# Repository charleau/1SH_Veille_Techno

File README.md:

# 1SH Veille Technologique
 
## L'électronique fondamentale

### Contexte
La technologie est omniprésente dans la vie de chacun. Les circuits imprimés et les composantes électroniques sont le point central de cette technologie. Avec l'essor des technologies telles que l'Internet des objets (IoT), les véhicules autonomes, et la robotique, etc., la demande en systèmes électroniques efficaces et fiables n'a jamais été aussi élevée. La compréhension des principes fondamentaux ainsi que les composantes électronique est donc nécessaire.

### Objectif
Connaitre et comprendre le fonctionnement de chacun des composants de base essentiels en électronique.
- Utilité des composants
- Fonctionnement des composants
- Schéma de circuit imprimé
- Exemples d'utilisation

### Démarche de [recherche](https://github.com/charleau/1SH_Veille_Techno/blob/main/Recherches.md)
- Phase I
    - [Lister les différents composants](https://github.com/charleau/1SH_Veille_Techno/blob/main/Recherches.md#composantes)
    - Identifier leur utilité
- Phase II
    - Comprendre le fonctionnement des composants
    - [Démontrer la bonne façon de brancher les composants](https://github.com/charleau/1SH_Veille_Techno/blob/main/Recherches.md#sch%C3%A9ma-%C3%A9lectrique)
- Phase III
    - [Concevoir un schéma de circuit appliquant les composants de base](https://github.com/charleau/1SH_Veille_Techno/blob/main/Recherches.md#conception-du-circuit-imprim%C3%A9)

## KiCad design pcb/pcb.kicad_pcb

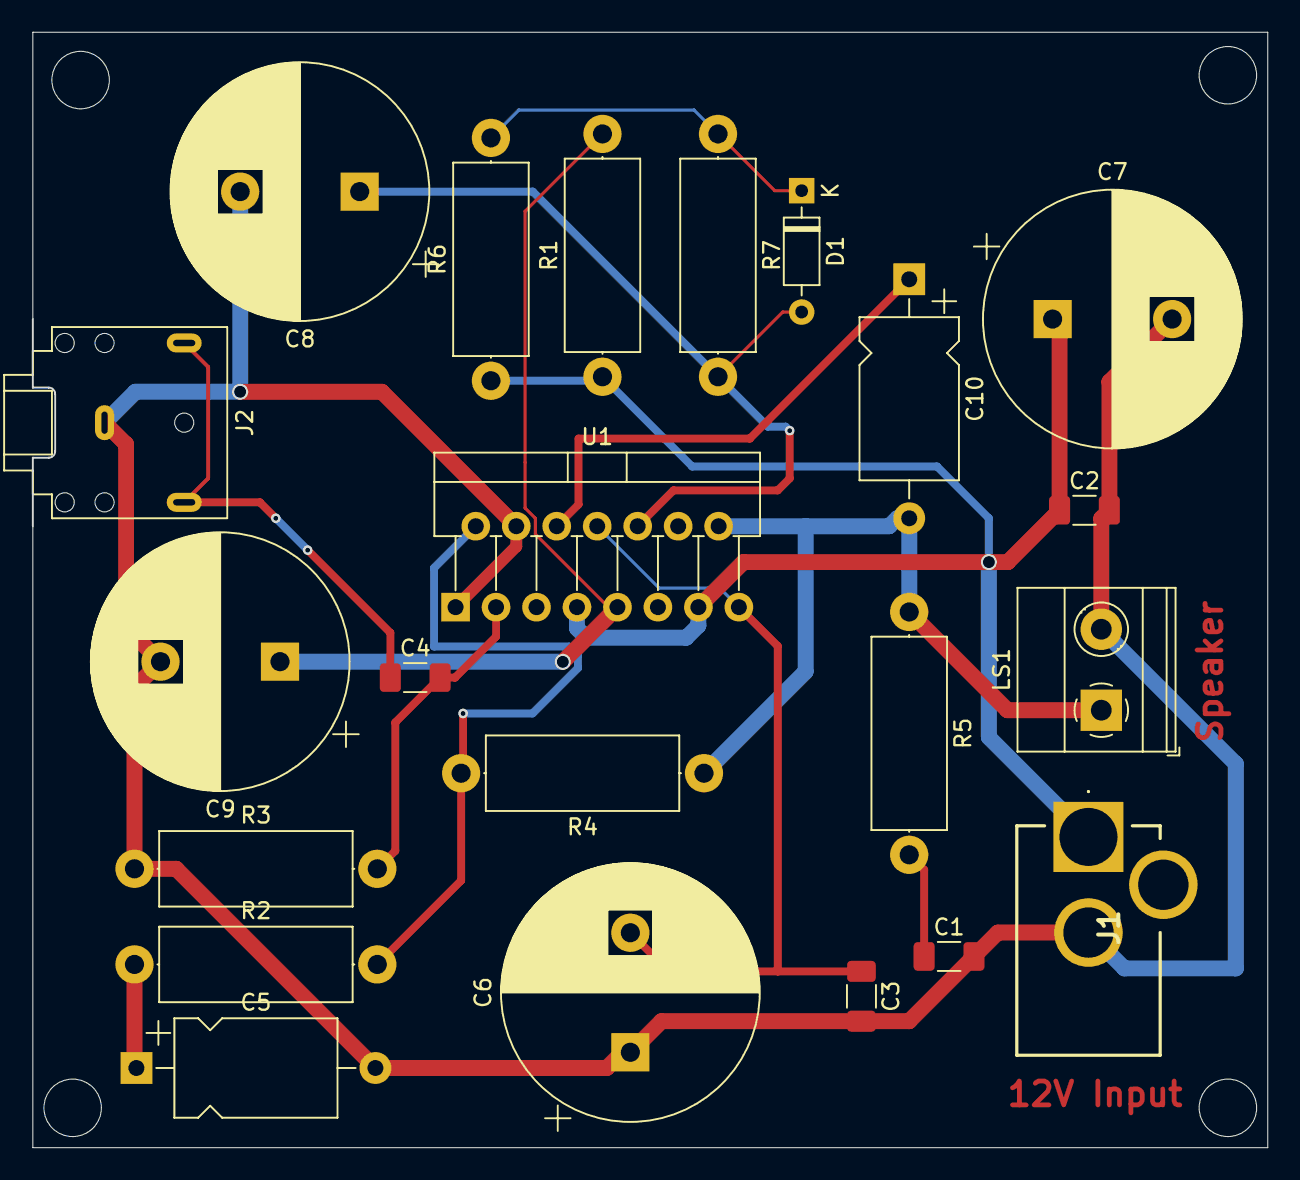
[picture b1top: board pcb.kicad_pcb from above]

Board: 2 copper layers, 77.5 x 69.9 mm, 22 parts (0 on the bottom side), 13 nets.

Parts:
C1, C2, C3: 100N; C_1206_3216Metric_Pad1.33x1.80mm_HandSolder
C4: 470N; C_1206_3216Metric_Pad1.33x1.80mm_HandSolder
C5, C10: 22µ; CP_Axial_L10.0mm_D6.0mm_P15.00mm_Horizontal
C6, C7: 1000µ; CP_Radial_D16.0mm_P7.50mm
C8, C9: 10µ; CP_Radial_D16.0mm_P7.50mm
D1: 1N4148; D_DO-35_SOD27_P7.62mm_Horizontal
J1: Conn_Coaxial_Power; PJ202AH
J2: AudioJack3; Jack_3.5mm_CUI_SJ1-3523N_Horizontal
LS1: Speaker; TerminalBlock_Phoenix_MKDS-1,5-2-5.08_1x02_P5.08mm_Horizont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
R1, R3, R4: 22k; R_Axial_DIN0414_L11.9mm_D4.5mm_P15.24mm_Horizontal
R2: R680; R_Axial_DIN0414_L11.9mm_D4.5mm_P15.24mm_Horizontal
R5: R2.2; R_Axial_DIN0414_L11.9mm_D4.5mm_P15.24mm_Horizontal
R6: 10k; R_Axial_DIN0414_L11.9mm_D4.5mm_P15.24mm_Horizontal
R7: 33k; R_Axial_DIN0414_L11.9mm_D4.5mm_P15.24mm_Horizontal
U1: TDA7294; TO-220-15_P2.54x2.54mm_StaggerOdd_Lead4.58mm_Vertical

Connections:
GND: C1.2, C2.2, C3.2, C5.2, C6.1, C7.2, C8.2, C9.2, J1.2 (Ext), J2.S, LS1.2, R3.1, U1.1 (SGND), U1.4 (SIG_GND)
unnamed: C1.1, R5.2
unnamed: C4.1, J2.R, J2.T
unnamed: C5.1, R2.1
unnamed: C10.2, LS1.1, R4.1, R5.1, U1.14
unnamed: C8.1, D1.2 (A), R7.2, U1.10 (MUTE)
unnamed: D1.1 (K), R6.2, R7.1
unnamed: C3.1, C6.2, U1.8 (-Vs), U1.15 (-Vs)
unnamed: C2.1, C7.1, J1.1 (In), R1.1, R6.1, U1.7 (+Vs), U1.13 (+Vs)
unnamed: C4.2, R3.2, U1.3 (+)
unnamed: R2.2, R4.2, U1.2 (-)
unnamed: C10.1, U1.6 (BOOT)
unnamed: C9.1, R1.2, U1.9 (STBY)

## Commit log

2024-04-29 Ajout carte mentale
2024-04-29 Ajout pdf carte mentale
2024-05-27 thermistance md
2024-05-27 move image to img folder
2024-05-27 try img
2024-05-27 try size img
2024-05-27 try anoter size of img
2024-05-27 Ajout condensateur
2024-05-28 Ajout résistance
2024-05-28 Ajout diode
2024-05-28 ajout transistor
2024-05-28 ajout varistor
2024-05-28 Ajout base Notes_conference
2024-05-28 Ajout responsabilité contractuelle
2024-05-28 Update notes conférence
2024-05-28 Ajout droit de l'entreprise
2024-05-28 Ajout droit du travail notes conférence
2024-05-28 Update notes conference
2024-05-28 Ajout photorésistance
2024-05-28 Ajout inductance et potentiomètre
2024-05-28 Ajout du courant
2024-05-29 Update recherche
2024-05-29 Add table of content
2024-05-29 Ajout CC vs CA
2024-05-29 Update recherches
2024-05-31 Test
2024-05-31 Update path imgs
2024-06-03 Ajout PCB KiCad
2024-06-03 Ajout captures d'écran conception
2024-06-03 Update PCB
2024-06-04 Ajout intro & desc. projet
2024-06-04 Ajout création kicad & schema
2024-06-05 Doc conception schéma complétée
2024-06-05 Reformat
2024-06-05 Correction fr
2024-06-05 Update PCB & recherches
2024-06-05 doc création pcb terminée
2024-06-06 ajout Exportation en GERBER recherches
2024-06-06 Ajout Difficultés et facilitées & conclusion à la recherche
2024-06-06 Ajout powerpoint présentation
2024-06-06 Update powerpoint
